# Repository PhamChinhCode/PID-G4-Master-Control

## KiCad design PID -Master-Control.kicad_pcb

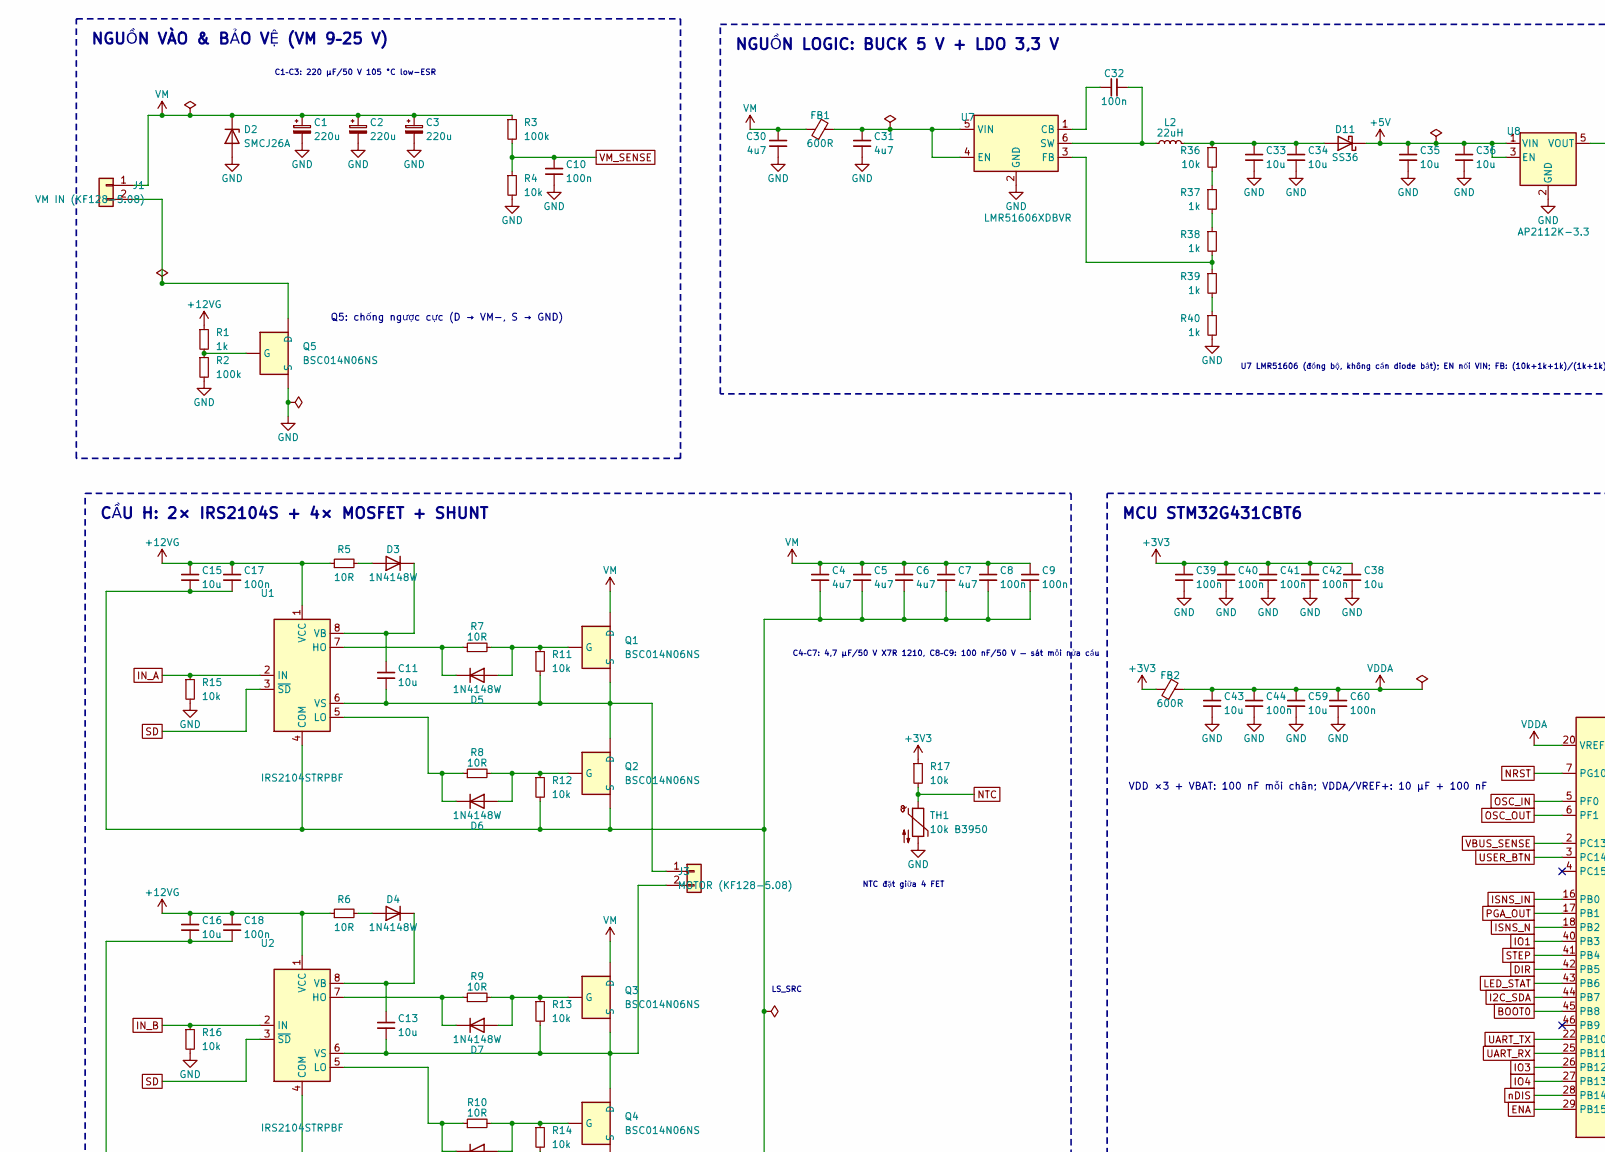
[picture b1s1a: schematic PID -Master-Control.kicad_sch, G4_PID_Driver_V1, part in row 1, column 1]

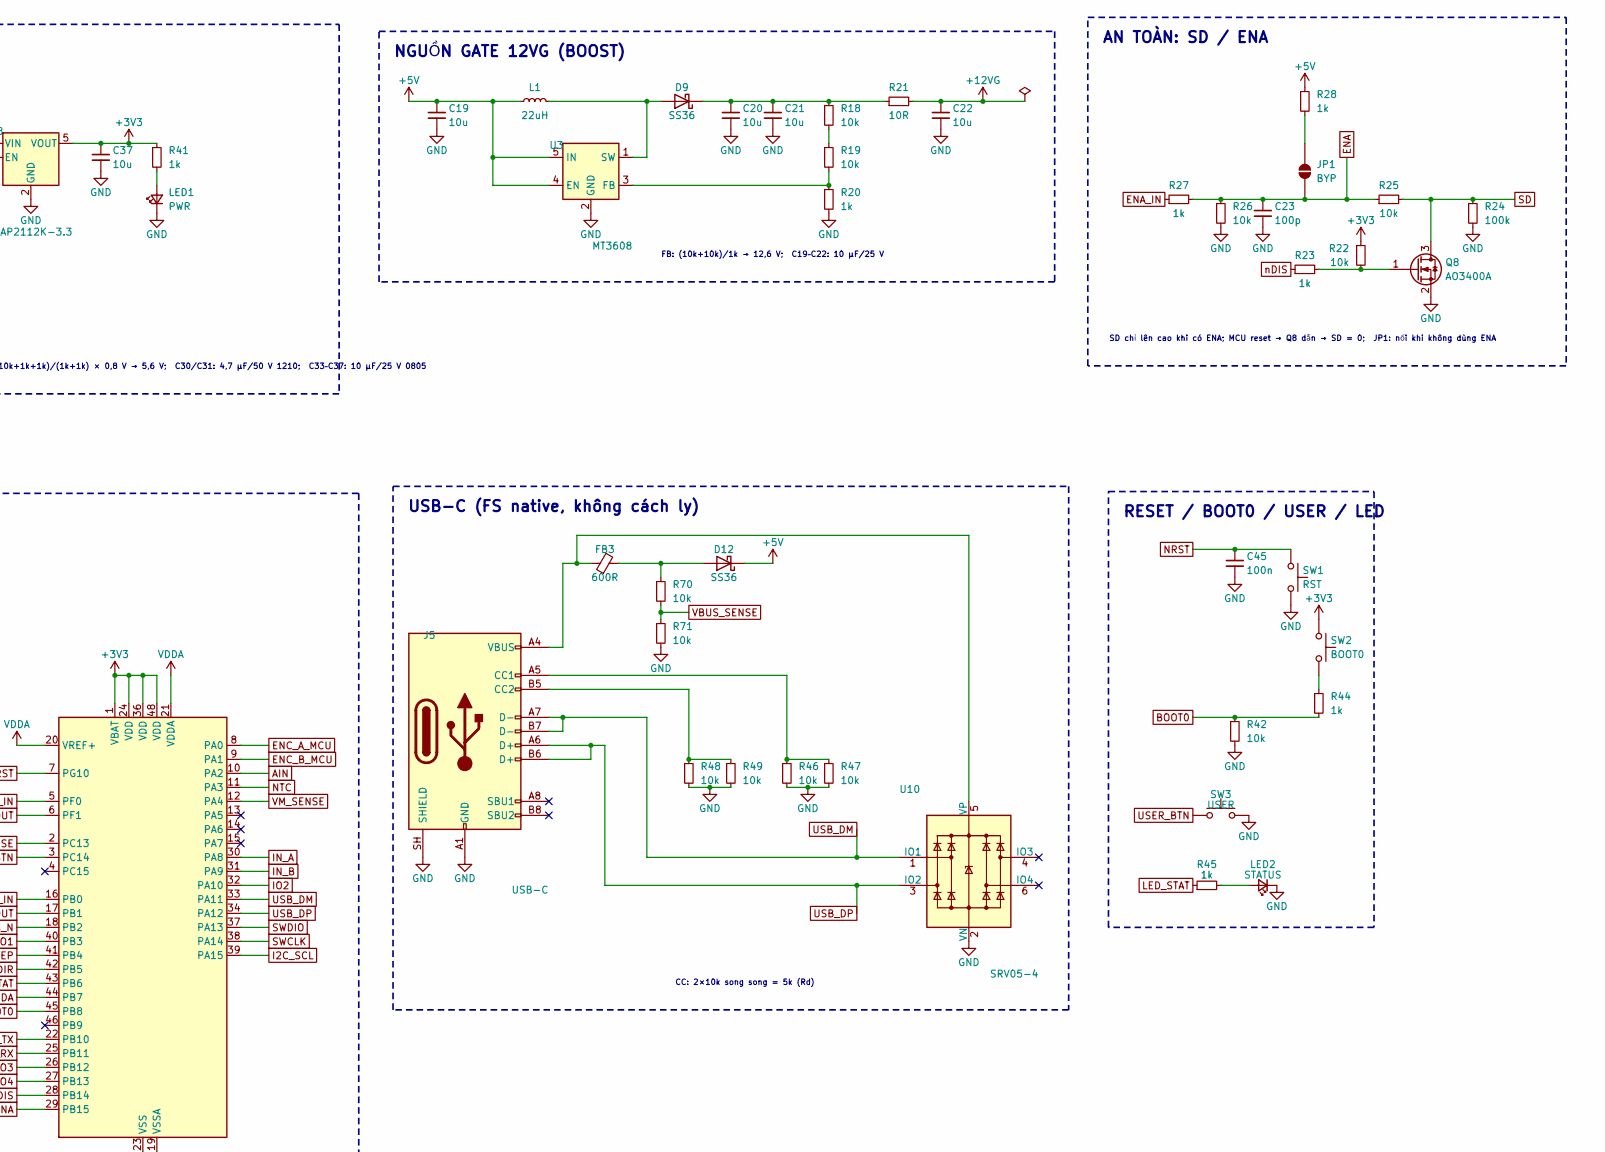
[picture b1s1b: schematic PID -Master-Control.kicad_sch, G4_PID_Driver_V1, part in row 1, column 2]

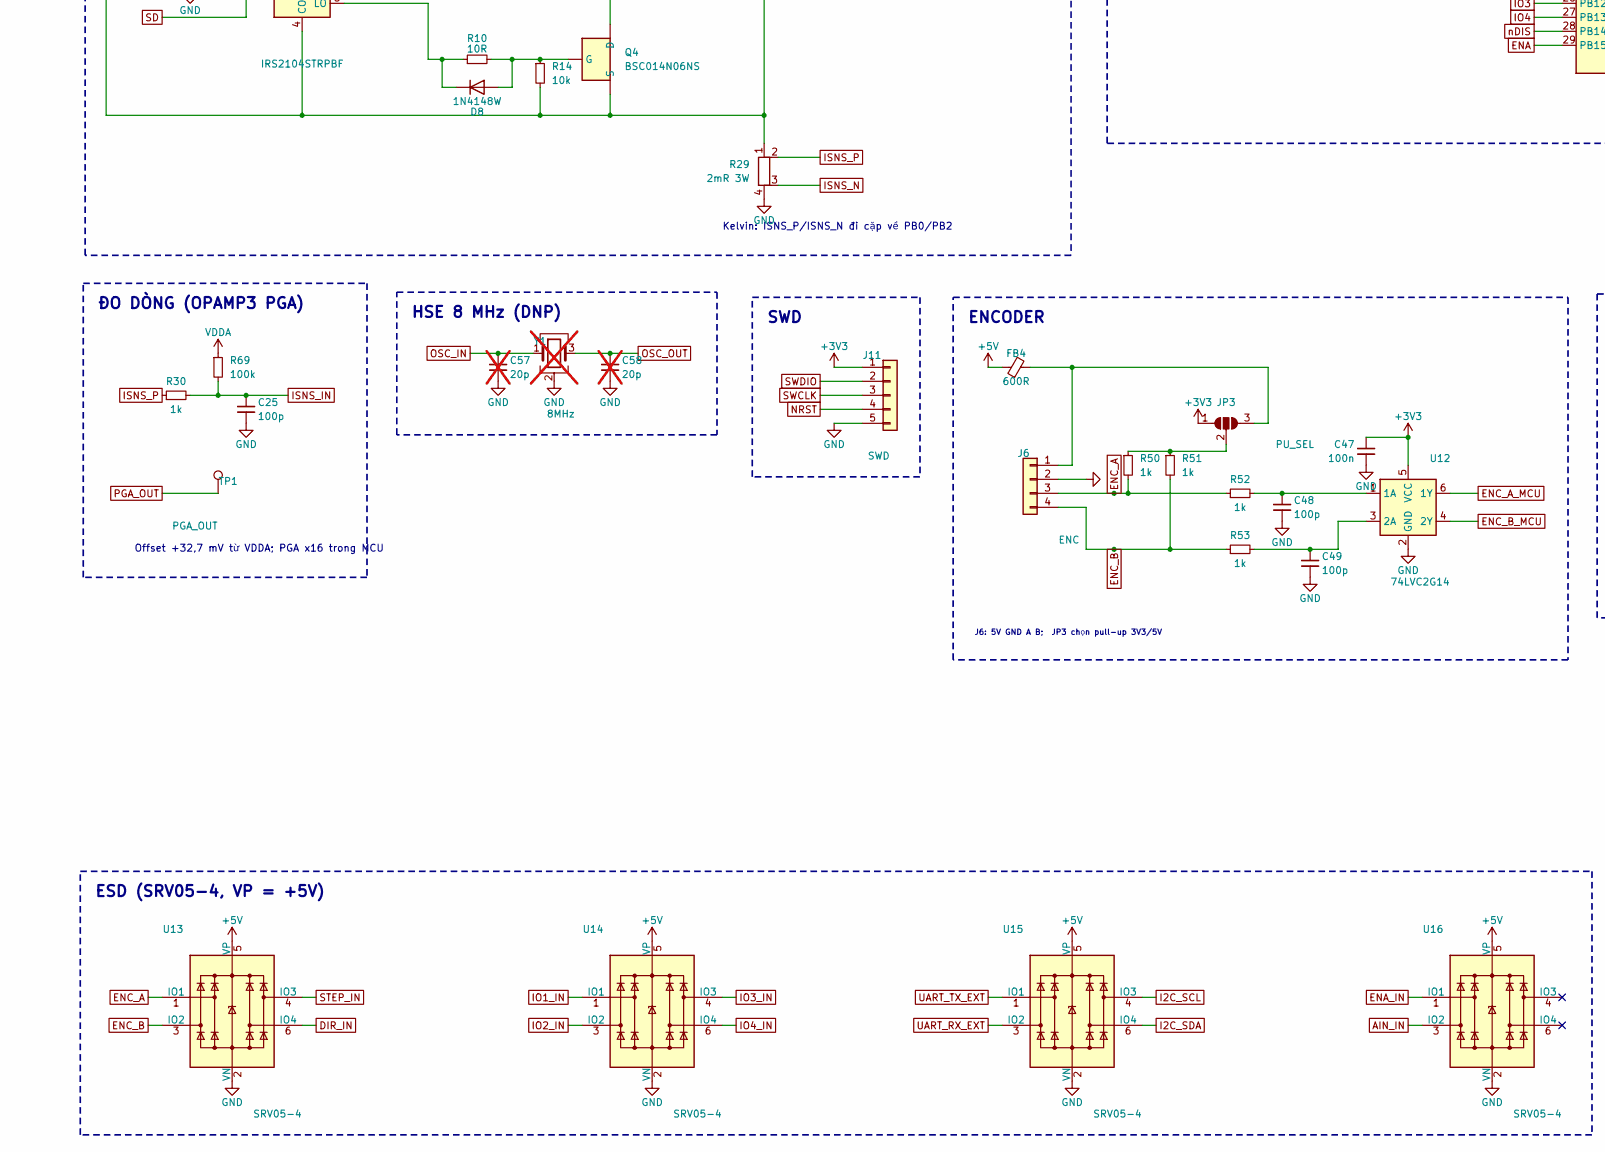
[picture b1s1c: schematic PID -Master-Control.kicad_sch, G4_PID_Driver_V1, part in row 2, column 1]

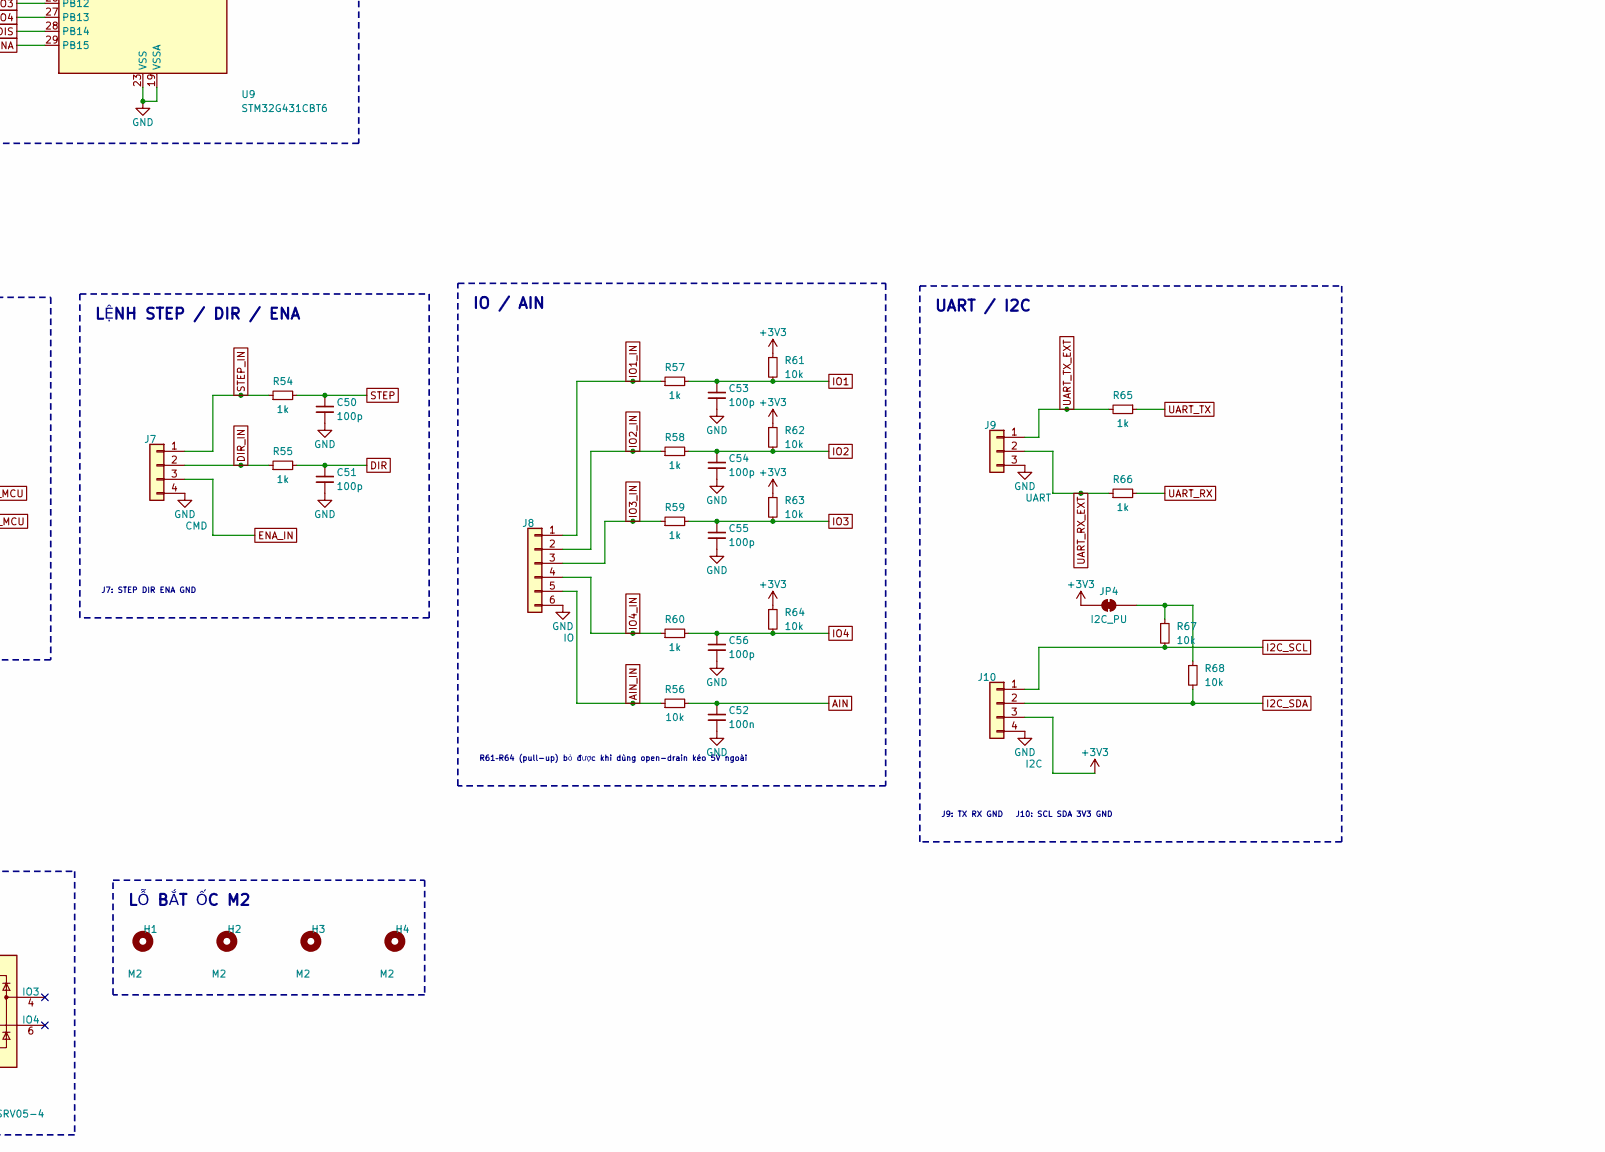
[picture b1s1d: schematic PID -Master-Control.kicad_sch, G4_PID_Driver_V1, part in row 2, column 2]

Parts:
C1, C2, C3: 220u; CP_Elec_10x10.5
C4, C5, C6, C7, C30, C31: 4u7; C_1210_3225Metric
C8, C9, C10, C17, C18, C32, C39, C40, C41, C42, C44, C45, C47, C52, C60: 100n; C_0603_1608Metric
C11, C13, C15, C16, C19, C20, C21, C22, C33, C34, C35, C36, C37, C38, C43, C59: 10u; C_0805_2012Metric
C23, C25, C48, C49, C50, C51, C53, C54, C55, C56: 100p; C_0603_1608Metric
C57, C58: 20p; C_0603_1608Metric; not fitted
D2: SMCJ26A; D_SMC
D3, D4, D5, D6, D7, D8: 1N4148W; D_SOD-123
D9, D11, D12: SS36; D_SMA
FB1, FB2, FB3, FB4: 600R; L_0805_2012Metric
H1, H2, H3, H4: M2; MountingHole_2.2mm_M2
J1: VM IN (KF128-5.08); KF128-5.08-2P
J3: MOTOR (KF128-5.08); KF128-5.08-2P
J5: USB-C; USB_C_Receptacle_HRO_TYPE-C-31-M-12
J6: ENC; JST_XH_S4B-XH-A_1x04_P2.50mm_Horizontal
J7: CMD; JST_XH_S4B-XH-A_1x04_P2.50mm_Horizontal
J8: IO; JST_XH_S6B-XH-A_1x06_P2.50mm_Horizontal
J9: UART; JST_XH_S3B-XH-A_1x03_P2.50mm_Horizontal
J10: I2C; JST_XH_S4B-XH-A_1x04_P2.50mm_Horizontal
J11: SWD; JST_XH_S5B-XH-A_1x05_P2.50mm_Horizontal
JP1: BYP; SolderJumper-2_P1.3mm_Open_RoundedPad1.0x1.5mm
JP3: PU_SEL; SolderJumper-3_P1.3mm_Open_RoundedPad1.0x1.5mm_NumberLabels
JP4: I2C_PU; SolderJumper-2_P1.3mm_Bridged_RoundedPad1.0x1.5mm
L1, L2: 22uH; L_Bourns-SRN4018
LED1: PWR; LED_0603_1608Metric
LED2: STATUS; LED_0603_1608Metric
Q1, Q2, Q3, Q4, Q5: BSC014N06NS; TDSON-8-1
Q8: AO3400A; SOT-23
R1, R20, R23, R27, R28, R30, R37, R38, R39, R40, R41, R44, R45, R50, R51, R52, R53, R54, R55, R57, R58, R59, R60, R65, R66: 1k; R_0603_1608Metric
R2, R3, R24, R69: 100k; R_0603_1608Metric
R4, R11, R12, R13, R14, R15, R16, R17, R18, R19, R22, R25, R26, R36, R42, R46, R47, R48, R49, R56, R61, R62, R63, R64, R67, R68, R70, R71: 10k; R_0603_1608Metric
R5, R6, R7, R8, R9, R10, R21: 10R; R_0603_1608Metric
R29: 2mR 3W; R_Shunt_Vishay_WSK2512_6332Metric_T1.19mm
SW1: RST; SW_SPST_PTS810
SW2: BOOT0; SW_SPST_PTS810
SW3: USER; SW_SPST_PTS810
TH1: 10k B3950; R_0603_1608Metric
TP1: PGA_OUT; TestPoint_Pad_D1.5mm
U1, U2: IRS2104STRPBF; SOIC-8_3.9x4.9mm_P1.27mm
U3: MT3608; SOT-23-6
U7: LMR51606XDBVR; SOT-23-6
U8: AP2112K-3.3; SOT-23-5
U9: STM32G431CBT6; LQFP-48_7x7mm_P0.5mm
U10, U13, U14, U15, U16: SRV05-4; SOT-23-6
U12: 74LVC2G14; SOT-23-6
Y1: 8MHz; Crystal_SMD_3225-4Pin_3.2x2.5mm; not fitted

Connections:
+3V3: C37.1, C38.1, C39.1, C40.1, C41.1, C42.1, C47.1, FB2.1, J10.3, J11.1, JP3.1 (A), JP4.1 (A), R17.1, R22.1, R41.1, R61.1, R62.1, R63.1, R64.1, SW2.1, U8.5 (VOUT), U9.1 (VBAT), U9.24 (VDD), U9.36 (VDD), U9.48 (VDD), U12.5 (VCC)
+5V: C19.1, C35.1, C36.1, D11.1 (K), D12.1 (K), FB4.1, L1.1, R28.1, U3.4 (EN), U3.5 (IN), U8.1 (VIN), U8.3 (EN), U13.5 (VP), U14.5 (VP), U15.5 (VP), U16.5 (VP)
+12VG: C15.1, C16.1, C17.1, C18.1, C22.1, R1.1, R5.1, R6.1, R21.2, U1.1 (VCC), U2.1 (VCC)
AIN: C52.1, R56.2, U9.10 (PA2)
AIN_IN: J8.5, R56.1, U16.3 (IO2)
BOOT0: R42.1, R44.2, U9.45 (PB8)
DIR: C51.1, R55.2, U9.42 (PB5)
DIR_IN: J7.2, R55.1, U13.6 (IO4)
ENA: C23.1, JP1.2 (B), R25.1, R26.1, R27.2, U9.29 (PB15)
ENA_IN: J7.3, R27.1, U16.1 (IO1)
ENC_A: J6.3, R50.2, R52.1, U13.1 (IO1)
ENC_A_MCU: U9.8 (PA0), U12.6 (1Y)
ENC_B: J6.4, R51.2, R53.1, U13.3 (IO2)
ENC_B_MCU: U9.9 (PA1), U12.4 (2Y)
GND: C1.2, C2.2, C3.2, C10.2, C19.2, C20.2, C21.2, C22.2, C23.2, C25.2, C30.2, C31.2, C33.2, C34.2, C35.2, C36.2, C37.2, C38.2, C39.2, C40.2, C41.2, C42.2, C43.2, C44.2, C45.2, C47.2, C48.2, C49.2, C50.2, C51.2, C52.2, C53.2, C54.2, C55.2, C56.2, C57.2, C58.2, C59.2, C60.2, D2.2 (A), J5.A1 (GND), J5.A12 (GND), J5.B1 (GND), J5.B12 (GND), J5.SH (SHIELD), J6.2, J7.4, J8.6, J9.3, J10.4, J11.5, LED1.1 (K), LED2.1 (K), Q5.1 (S), Q5.2 (S), Q5.3 (S), Q8.2 (S), R2.2, R4.2, R15.2, R16.2, R20.2, R24.2, R26.2, R29.4, R40.2, R42.2, R46.2, R47.2, R48.2, R49.2, R71.2, SW1.2, SW3.2, TH1.2, U3.2 (GND), U7.2 (GND), U8.2 (GND), U9.19 (VSSA), U9.23 (VSS), U9.35 (VSS), U9.47 (VSS), U10.2 (VN), U12.2 (GND), U13.2 (VN), U14.2 (VN), U15.2 (VN), U16.2 (VN), Y1.2 (G), Y1.4 (G)
I2C_SCL: J10.1, R67.2, U9.39 (PA15), U15.4 (IO3)
I2C_SDA: J10.2, R68.2, U9.44 (PB7), U15.6 (IO4)
IN_A: R15.1, U1.2 (IN), U9.30 (PA8)
IN_B: R16.1, U2.2 (IN), U9.31 (PA9)
IO1: C53.1, R57.2, R61.2, U9.40 (PB3)
IO1_IN: J8.1, R57.1, U14.1 (IO1)
IO2: C54.1, R58.2, R62.2, U9.32 (PA10)
IO2_IN: J8.2, R58.1, U14.3 (IO2)
IO3: C55.1, R59.2, R63.2, U9.26 (PB12)
IO3_IN: J8.3, R59.1, U14.4 (IO3)
IO4: C56.1, R60.2, R64.2, U9.27 (PB13)
IO4_IN: J8.4, R60.1, U14.6 (IO4)
ISNS_IN: C25.1, R30.2, R69.2, U9.16 (PB0)
ISNS_N: R29.3, U9.18 (PB2)
ISNS_P: R29.2, R30.1
LED_STAT: R45.1, U9.43 (PB6)
NRST: C45.1, J11.4, SW1.1, U9.7 (PG10)
NTC: R17.2, TH1.1, U9.11 (PA3)
unnamed: D3.2 (A), R5.2
unnamed: C11.1, D3.1 (K), U1.8 (VB)
unnamed: D4.2 (A), R6.2
unnamed: C13.1, D4.1 (K), U2.8 (VB)
unnamed: D5.2 (A), Q1.4 (G), R7.2, R11.1
unnamed: D5.1 (K), R7.1, U1.7 (HO)
unnamed: D6.2 (A), Q2.4 (G), R8.2, R12.1
unnamed: D6.1 (K), R8.1, U1.5 (LO)
unnamed: D7.2 (A), Q3.4 (G), R9.2, R13.1
unnamed: D7.1 (K), R9.1, U2.7 (HO)
unnamed: D8.2 (A), Q4.4 (G), R10.2, R14.1
unnamed: D8.1 (K), R10.1, U2.5 (LO)
unnamed: D9.2 (A), L1.2, U3.1 (SW)
unnamed: C20.1, C21.1, D9.1 (K), R18.1, R21.1
unnamed: C33.1, C34.1, D11.2 (A), L2.2, R36.1
unnamed: D12.2 (A), FB3.2, R70.1
unnamed: J1.2, Q5.5 (D)
unnamed: C11.2, J3.1, Q1.1 (S), Q1.2 (S), Q1.3 (S), Q2.5 (D), R11.2, U1.6 (VS)
unnamed: C13.2, J3.2, Q3.1 (S), Q3.2 (S), Q3.3 (S), Q4.5 (D), R13.2, U2.6 (VS)
unnamed: J5.A5 (CC1), R46.1, R47.1
unnamed: J5.B5 (CC2), R48.1, R49.1
unnamed: FB4.2, J6.1, JP3.3 (B)
unnamed: JP1.1 (A), R28.2
unnamed: JP3.2 (C), R50.1, R51.1
unnamed: JP4.2 (B), R67.1, R68.1
unnamed: LED1.2 (A), R41.2
unnamed: LED2.2 (A), R45.2
unnamed: Q5.4 (G), R1.2, R2.1
unnamed: Q8.1 (G), R22.2, R23.2
unnamed: R18.2, R19.1
unnamed: R36.2, R37.1
unnamed: R37.2, R38.1
unnamed: R39.2, R40.1
unnamed: R44.1, SW2.2
unnamed: C4.2, C5.2, C6.2, C7.2, C8.2, C9.2, C15.2, C16.2, C17.2, C18.2, Q2.1 (S), Q2.2 (S), Q2.3 (S), Q4.1 (S), Q4.2 (S), Q4.3 (S), R12.2, R14.2, R29.1, U1.4 (COM), U2.4 (COM)
unnamed: R19.2, R20.1, U3.3 (FB)
unnamed: C32.1, U7.1 (CB)
unnamed: C31.1, FB1.2, U7.4 (EN), U7.5 (VIN)
unnamed: R38.2, R39.1, U7.3 (FB)
unnamed: C32.2, L2.1, U7.6 (SW)
unnamed: FB3.1, J5.A4 (VBUS), J5.A9 (VBUS), J5.B4 (VBUS), J5.B9 (VBUS), U10.5 (VP)
unnamed: C48.1, R52.2, U12.1 (1A)
unnamed: C49.1, R53.2, U12.3 (2A)
OSC_IN: C57.1, U9.5 (PF0), Y1.1
OSC_OUT: C58.1, U9.6 (PF1), Y1.3
PGA_OUT: TP1.1, U9.17 (PB1)
SD: Q8.3 (D), R24.1, R25.2, U1.3 (~SD), U2.3 (~SD)
STEP: C50.1, R54.2, U9.41 (PB4)
STEP_IN: J7.1, R54.1, U13.4 (IO3)
SWCLK: J11.3, U9.38 (PA14)
SWDIO: J11.2, U9.37 (PA13)
UART_RX: R66.2, U9.25 (PB11)
UART_RX_EXT: J9.2, R66.1, U15.3 (IO2)
UART_TX: R65.1, U9.22 (PB10)
UART_TX_EXT: J9.1, R65.2, U15.1 (IO1)
USB_DM: J5.A7 (D-), J5.B7 (D-), U9.33 (PA11), U10.1 (IO1)
USB_DP: J5.A6 (D+), J5.B6 (D+), U9.34 (PA12), U10.3 (IO2)
USER_BTN: SW3.1, U9.3 (PC14)
VBUS_SENSE: R70.2, R71.1, U9.2 (PC13)
VDDA: C43.1, C44.1, C59.1, C60.1, FB2.2, R69.1, U9.20 (VREF+), U9.21 (VDDA)
VM: C1.1, C2.1, C3.1, C4.1, C5.1, C6.1, C7.1, C8.1, C9.1, C30.1, D2.1 (K), FB1.1, J1.1, Q1.5 (D), Q3.5 (D), R3.1
VM_SENSE: C10.1, R3.2, R4.1, U9.12 (PA4)
nDIS: R23.1, U9.28 (PB14)

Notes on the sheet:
VDD ×3 + VBAT: 100 nF mỗi chân; VDDA/VREF+: 10 µF + 100 nF
NGUỒN VÀO & BẢO VỆ (VM 9–25 V)
C4–C7: 4,7 µF/50 V X7R 1210, C8–C9: 100 nF/50 V — sát mỗi nửa cầu
IO / AIN
U7 LMR51606 (đồng bộ, không cần diode bắt); EN nối VIN; FB: (10k+1k+1k)/(1k+1k) × 0,8 V → 5,6 V; C30/C31: 4,7 µF/50 V 1210; C33–C37: 10 µF/25 V 0805
J6: 5V GND A B; JP3 chọn pull-up 3V3/5V
SD chỉ lên cao khi có ENA; MCU reset → Q8 dẫn → SD = 0; JP1: nối khi không dùng ENA
SWD
CC: 2×10k song song = 5k (Rd)
ENCODER
AN TOÀN: SD / ENA
UART / I2C
Q5: chống ngược cực (D → VM−, S → GND)
NGUỒN LOGIC: BUCK 5 V + LDO 3,3 V
HSE 8 MHz (DNP)
FB: (10k+10k)/1k → 12,6 V; C19–C22: 10 µF/25 V
NGUỒN GATE 12VG (BOOST)
Offset +32,7 mV từ VDDA; PGA x16 trong MCU
MCU STM32G431CBT6
RESET / BOOT0 / USER / LED
J9: TX RX GND J10: SCL SDA 3V3 GND
NTC đặt giữa 4 FET
LỆNH STEP / DIR / ENA
C1–C3: 220 µF/50 V 105 °C low-ESR
LS_SRC
Kelvin: ISNS_P/ISNS_N đi cặp về PB0/PB2
ĐO DÒNG (OPAMP3 PGA)
ESD (SRV05-4, VP = +5V)
R61–R64 (pull-up) bỏ được khi dùng open-drain kéo 5V ngoài
J7: STEP DIR ENA GND
LỖ BẮT ỐC M2
USB-C (FS native, không cách ly)
CẦU H: 2× IRS2104S + 4× MOSFET + SHUNT

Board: 4 copper layers, 175 parts (0 on the bottom side), 96 nets, no tracks yet.
